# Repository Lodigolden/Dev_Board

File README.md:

# Dev_Board
A development board to test hardware stuff.

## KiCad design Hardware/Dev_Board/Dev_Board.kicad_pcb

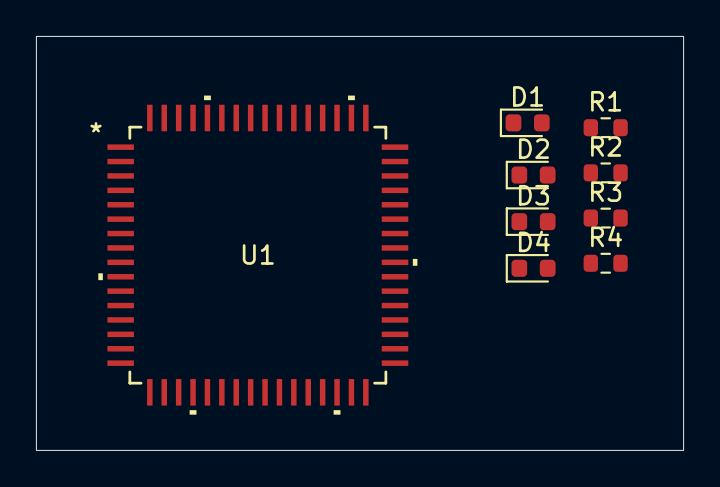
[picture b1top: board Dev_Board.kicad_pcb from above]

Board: 2 copper layers, 36.0 x 23.0 mm, 9 parts (0 on the bottom side), 10 nets, no tracks yet.

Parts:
D1, D2, D3, D4: LED; LED_0603_1608Metric
R1, R2, R3, R4: 1k; R_0603_1608Metric
U1: AT90USB1287-AUR; TQFP64_ATM

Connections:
+3V3: U1.20 (RESET), U1.21 (VCC), U1.52 (VCC)
GND: R1.2, R2.2, R3.2, R4.2, U1.6 (UGnd), U1.22 (GND), U1.53 (GND), U1.63 (GND)
unnamed: D1.2 (A), U1.48 (PA3_(AD3))
unnamed: D1.1 (K), R1.1
unnamed: D2.2 (A), U1.49 (PA2_(AD2))
unnamed: D2.1 (K), R2.1
unnamed: D3.2 (A), U1.50 (PA1_(AD1))
unnamed: D3.1 (K), R3.1
unnamed: D4.2 (A), U1.51 (PA0_(AD0))
unnamed: D4.1 (K), R4.1

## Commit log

2024-12-03 Initial mcu setup
2024-12-06 Added EEPROM documentation
2024-12-10 Added the temperature sensor
